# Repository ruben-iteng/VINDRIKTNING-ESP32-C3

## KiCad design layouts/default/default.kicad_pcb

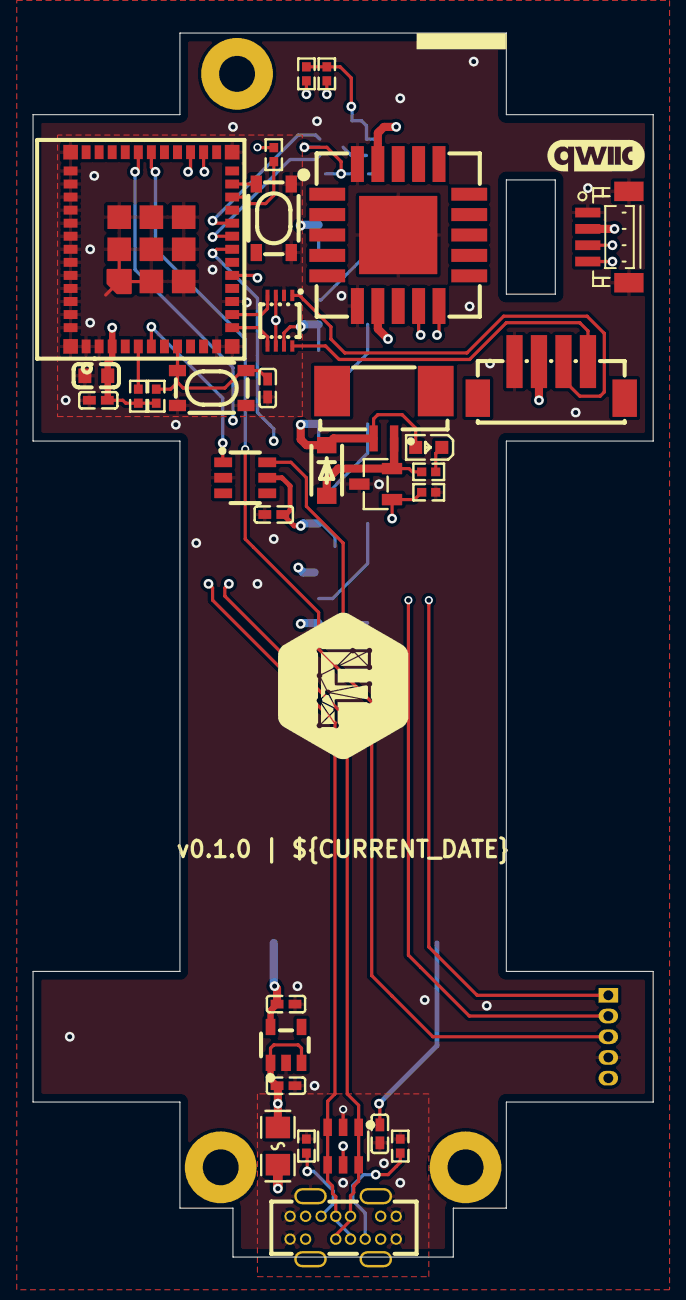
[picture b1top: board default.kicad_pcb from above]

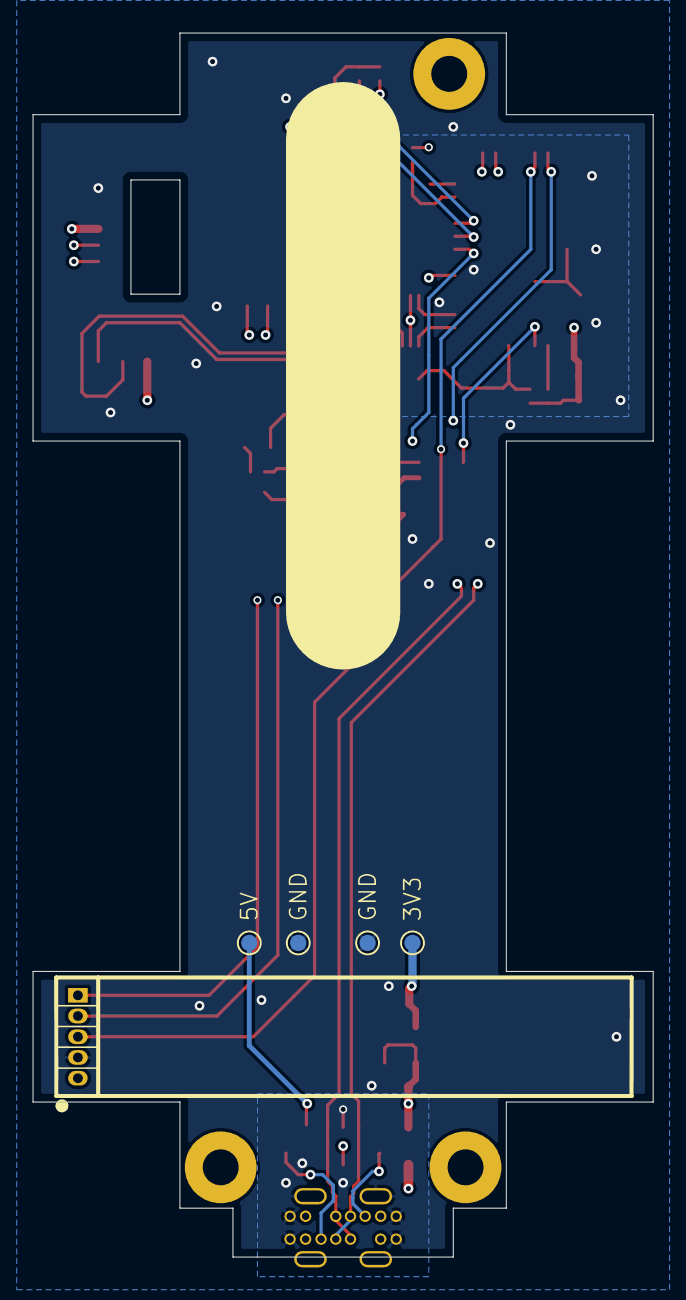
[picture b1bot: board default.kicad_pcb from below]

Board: 4 copper layers, 38.0 x 75.0 mm, 56 parts (18 on the bottom side), 31 nets.

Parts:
C1, C2, C3, C4, C5, C6, C7, C8, C9, C11, C13, C14: 100nF ±10% 16V X7R; C0402-b3ef17
C10: 22µF ±20% 6.3V X5R; C0603-bd72f6
C12: 1µF ±10% 25V X5R; C0402-b3ef17
CN1: CONN-SMD_BM04B-SRSS-TB-6963ef
D1: SOD-123F_L2.8-W1.8-LS3.7-RD-7788aa
FanConnector1: CONN-SMD_1.25-2P-ea2134
H1, H2, H3: MountingHole_2.2mm_M2_Pad
J2: CONN-SMD_ZH1.5-4AB-9aedad
LED1, LED2, LED3, LED4, LED5: LED-SMD_4P-L3.5-W2.8-BR-1-15b4e8
LOGO1: faebrykLogo_8x9mm
Q1: SOT-23-3_L2.9-W1.3-P1.90-LS2.4-BR-688f29
R1, R10: 1kΩ ±1% 62.5mW; R0402-56259e
R2, R6: 5.1kΩ ±1% 62.5mW; R0402-56259e
R3, R4, R5, R9, R11, R12: 10kΩ ±1% 62.5mW; R0402-56259e
TP1, TP2, TP3, TP4: TestPoint_Pad_D1.0mm
U1: LGA-20_L10.1-W10.1-P1.25-TL-a13bdd
U2: LDO 3.3V ±0% 850.5mA 320mV Vin max Iq 10µA; SOT-23-5_L2.9-W1.6-P0.95-LS2.8-BR-2dcca4
U3: SOT-23-6_L2.9-W1.6-P0.95-LS2.8-BR-bfc73b
U4: WSOF-6_L2.6-W1.6-P0.50-TL-EP-b2dfd8
U5, U7: KEY-SMD_4P-L4.2-W3.2-P2.20-LS4.6
U6: WIFIM-SMD_ESP32-C3-MINI-MINI-1U-1cb675
U8: SENSORM-TH_HLK-LD2410B-P-2a325e
U9: qwiic_6mm
U10: VSON8_L2.0-W2.3-P0.50-LS3.1-BL-9e6526
U11: 2V; LED0603-RD
U12: SOT-23-6_L2.9-W1.6-P0.95-LS2.8-BL-d2c740
U13: F0805-d5954a
X1: USB-C-TH_TYPE-C-USB-14P-1a34cb

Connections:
DVI: C13.1, R1.2, U4.5
cathode: R10.1, U11.1
gnd: C1.2, C2.2, C3.2, C4.2, C5.2, C6.2, C7.2, C8.2, C9.2, C10.2, C11.2, C12.2, C13.2, C14.2, CN1.0, CN1.1, J2.4, LED1.1, LED2.1, LED3.1, LED4.1, LED5.1, Q1.3, R2.2, R6.2, R9.2, TP2.1, TP4.1, U1.6, U1.20, U1.21, U2.2, U3.2, U4.2, U4.3, U4.7, U5.1, U5.2, U6.1, U6.2, U6.11, U6.14, U6.36, U6.37, U6.38, U6.39, U6.40, U6.41, U6.42, U6.43, U6.44, U6.45, U6.46, U6.47, U6.48, U6.49, U6.50, U6.51, U6.52, U6.53, U6.54, U6.55, U6.56, U6.57, U6.58, U6.59, U6.60, U6.61, U7.1, U7.2, U8.4, U10.2, U12.2, X1.0, X1.1, X1.7, X1.8, X1.14
hv: C1.1, C3.1, C4.1, C5.1, C6.1, C7.1, C8.1, C14.1, D1.1, FanConnector1.2, J2.3, LED1.3, LED2.3, LED3.3, LED4.3, LED5.3, TP3.1, U2.1, U2.3, U3.5, U8.5, U10.7, U11.2, U12.5, U13.2
hv-1: C2.1, C9.1, C10.1, C11.1, CN1.2, R1.1, R3.2, R4.2, R5.1, R11.2, R12.2, TP1.1, U1.7, U1.19, U2.5, U4.1, U6.3, U10.3, U10.6
hv-2: U13.1, X1.2, X1.6, X1.9, X1.13
line: LED1.4, LED2.2
line-1: CN1.4, R11.1, U1.9, U4.6, U6.20
line-2: LED4.4, LED5.2
line-3: Q1.1, R9.1, U6.18
line-4: R4.1, U6.22
line-6: U6.12, U10.5
line-7: U6.31, U8.2
line-8: CN1.3, R12.1, U1.10, U4.4, U6.19
line-9: U6.13, U10.4
line-10: LED2.4, LED3.2
line-11: R3.1, U6.5
line-12: U6.27, U12.3, U12.4, X1.4, X1.11
line-13: U6.16, U8.1
line-14: U3.1, U6.6
line-15: U6.26, U12.1, U12.6, X1.3, X1.10
line-16: R2.1, X1.12
line-17: LED1.2, U3.6
line-19: LED3.4, LED4.2
line-20: U6.30, U8.3
line-21: R6.1, X1.5
output: C12.1, R5.2, U6.8, U7.3, U7.4
output-1: U5.3, U5.4, U6.23
pin[0]: J2.1, U10.8
pin[1]: J2.2, U10.1
vindriktning_interface.fan_controller-gnd: D1.2, FanConnector1.1, Q1.2, R10.2

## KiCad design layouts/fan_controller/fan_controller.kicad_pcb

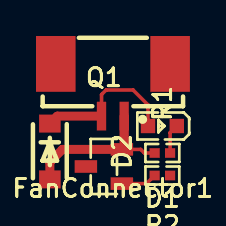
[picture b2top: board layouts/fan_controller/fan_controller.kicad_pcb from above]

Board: 2 copper layers, 6 parts (0 on the bottom side), 4 nets.

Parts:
D1: 2V; LED0603-RD
D2: SOD-123F_L2.8-W1.8-LS3.7-RD-7788aa
FanConnector1: CONN-SMD_1.25-2P-ea2134
Q1: SOT-23-3_L2.9-W1.3-P1.90-LS2.4-BR-688f29
R1: 10kΩ ±1% 62.5mW; R0402-56259e
R2: 1kΩ ±1% 62.5mW; R0402-56259e

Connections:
anode: D1.2, D2.1, FanConnector1.2
cathode: D1.1, R2.1
gate: Q1.1, R1.1
gnd: D2.2, FanConnector1.1, Q1.2, R2.2

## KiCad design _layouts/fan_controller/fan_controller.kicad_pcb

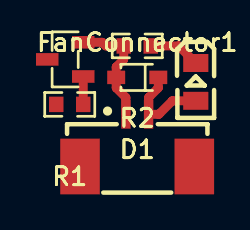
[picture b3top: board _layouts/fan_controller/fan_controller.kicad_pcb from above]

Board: 2 copper layers, 6 parts (0 on the bottom side), 4 nets.

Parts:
D1: 450mV; SOD-323_L1.8-W1.3-LS2.5-RD-b55baa
D2: LED0805-R-RD-d1137b
FanConnector1: CONN-SMD_1.25-2P-ea2134
Q1: SOT-23-3_L2.9-W1.3-P1.90-LS2.4-BL-1-fcaf94
R1, R2: 10kΩ ±1% 100mW; R0603-ebcab9

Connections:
cathode: D2.2, R2.1
gnd: D1.2, FanConnector1.1, Q1.2, R2.2
hv: D1.1, D2.1, FanConnector1.2
line: Q1.1, R1.1

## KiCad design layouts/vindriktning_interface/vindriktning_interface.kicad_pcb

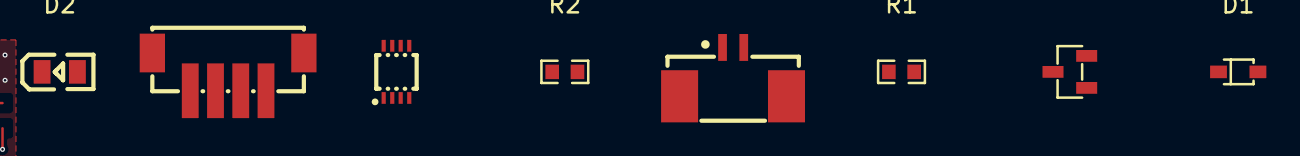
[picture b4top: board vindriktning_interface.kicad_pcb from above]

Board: 2 copper layers, 8 parts (0 on the bottom side), 9 nets.

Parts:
D1: 450mV; SOD-323_L1.8-W1.3-LS2.5-RD-b55baa
D2: LED0805-R-RD-d1137b
FanConnector1: CONN-SMD_1.25-2P-ea2134
J1: CONN-SMD_ZH1.5-4AB-9aedad
Q1: SOT-23-3_L2.9-W1.3-P1.90-LS2.4-BR-688f29
R1, R2: 10kΩ ±1% 100mW; R0603-ebcab9
U1: VSON8_L2.0-W2.3-P0.50-LS3.1-BL-9e6526

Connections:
cathode: D2.2, R2.1
fan_controller-gnd: D1.2, FanConnector1.1, Q1.2, R2.2
fan_controller-hv: D1.1, D2.1, FanConnector1.2
gnd-1: J1.4, U1.2
hv: J1.3, U1.7
hv-1: U1.3, U1.6
line: J1.2, U1.1
line-1: J1.1, U1.8
line-2: Q1.1, R1.1

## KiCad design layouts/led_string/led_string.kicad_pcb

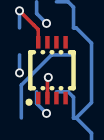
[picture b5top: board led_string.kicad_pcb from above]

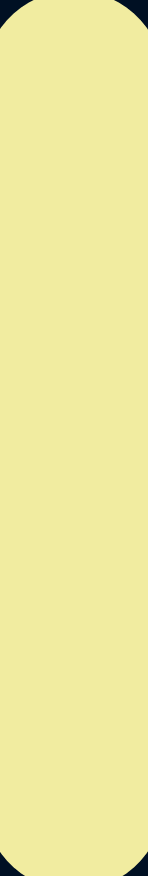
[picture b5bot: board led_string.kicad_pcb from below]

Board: 2 copper layers, 19 parts (18 on the bottom side), 12 nets.

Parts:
C1, C2, C3, C4, C5, C6, C7, C8, C9: 100nF ±10% 16V X7R; C0402-b3ef17
LED1, LED2, LED3, LED4, LED5, LED6, LED7, LED8, LED9: LED-SMD_4P-L3.5-W2.8-BR-1-15b4e8
U1: VSON8_L2.0-W2.3-P0.50-LS3.1-BL-9e6526

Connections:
gnd: C1.2, C2.2, C3.2, C4.2, C5.2, C6.2, C7.2, C8.2, C9.2, LED1.1, LED2.1, LED3.1, LED4.1, LED5.1, LED6.1, LED7.1, LED8.1, LED9.1, U1.2
hv: U1.3, U1.6
hv-1: C1.1, C2.1, C3.1, C4.1, C5.1, C6.1, C7.1, C8.1, C9.1, LED1.3, LED2.3, LED3.3, LED4.3, LED5.3, LED6.3, LED7.3, LED8.3, LED9.3, U1.7
line: LED4.4, LED5.2
line-1: LED5.4, LED6.2
line-2: LED1.2, U1.8
line-3: LED7.4, LED8.2
line-4: LED6.4, LED7.2
line-5: LED1.4, LED2.2
line-7: LED2.4, LED3.2
line-8: LED8.4, LED9.2
line-9: LED3.4, LED4.2

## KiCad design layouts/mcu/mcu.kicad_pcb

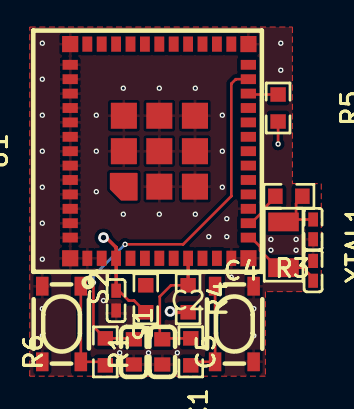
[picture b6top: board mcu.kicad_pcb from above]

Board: 2 copper layers, 15 parts (0 on the bottom side), 11 nets.

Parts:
C1, C5: 100nF ±10% 50V X7R; C0603-bd72f6
C2: 1µF ±10% 25V X5R; C0402-b3ef17
C3, C4: 20pF ±5% 50V C0G; C0402-b3ef17
R1, R2, R4, R5, R6: 10kΩ ±1% 100mW; R0603-ebcab9
R3: 0Ω 100mW; R0603-ebcab9
S1, S2: KEY-SMD_4P-L4.2-W3.2-P2.20-LS4.6-a2ccf0
U1: WIFIM-SMD_ESP32-C3-MINI-MINI-1U-1cb675
XTAL1: CRYSTAL-SMD_L3.2-W1.5-1-214bf9

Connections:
gnd: C1.2, C2.2, C3.2, C4.2, C5.2, S1.3, S1.4, S2.3, S2.4, U1.1, U1.2, U1.11, U1.14, U1.36, U1.37, U1.38, U1.39, U1.40, U1.41, U1.42, U1.43, U1.44, U1.45, U1.46, U1.47, U1.48, U1.49, U1.50, U1.51, U1.52, U1.53, U1.54, U1.55, U1.56, U1.57, U1.58, U1.59, U1.60, U1.61
hv: C2.1, R2.2, R4.2, R5.2, U1.3
mcu-line: C1.1, R1.2, R2.1, U1.8
mcu-line-1: C4.1, U1.12, XTAL1.2
mcu-line-4: R3.2, U1.13
mcu-line-5: R4.1, U1.5
mcu-line-7: C5.1, R6.2, U1.23
mcu-line-9: R5.1, U1.22
mcu.boot_switch-line: R1.1, S1.1, S1.2
mcu.low_speed_crystal_clock-net: C3.1, R3.1, XTAL1.1
mcu.reset_switch-line: R6.1, S2.1, S2.2

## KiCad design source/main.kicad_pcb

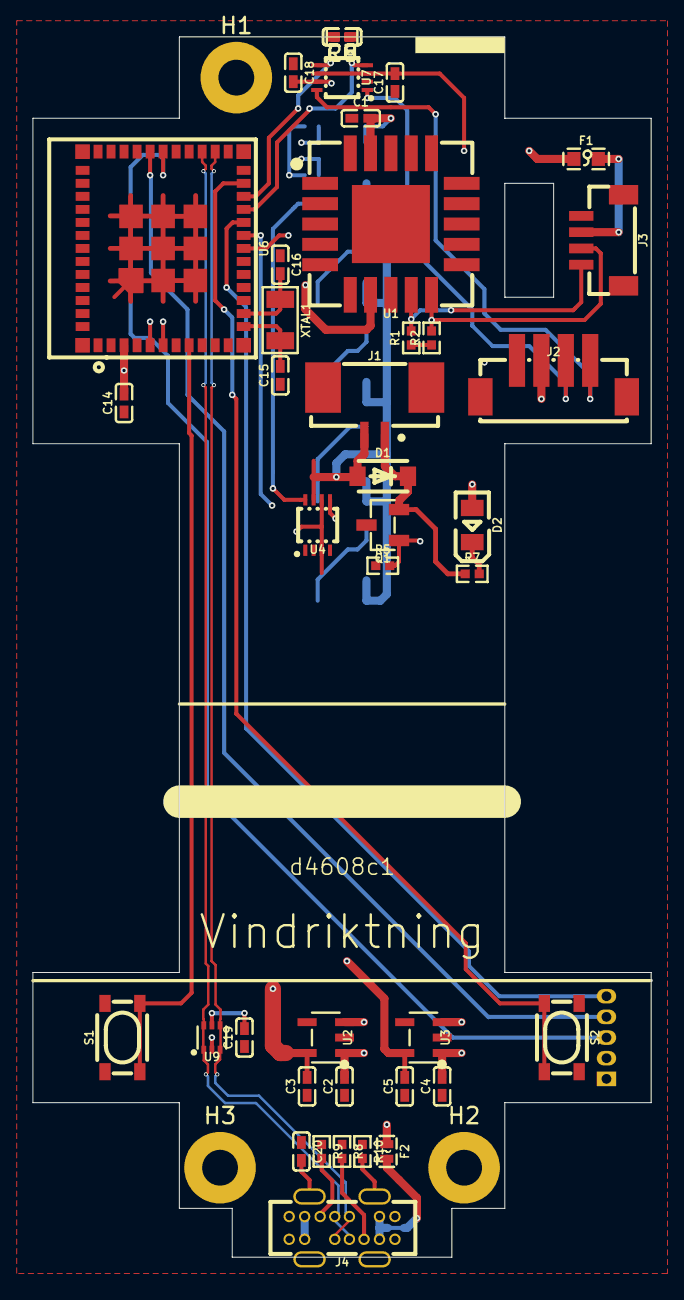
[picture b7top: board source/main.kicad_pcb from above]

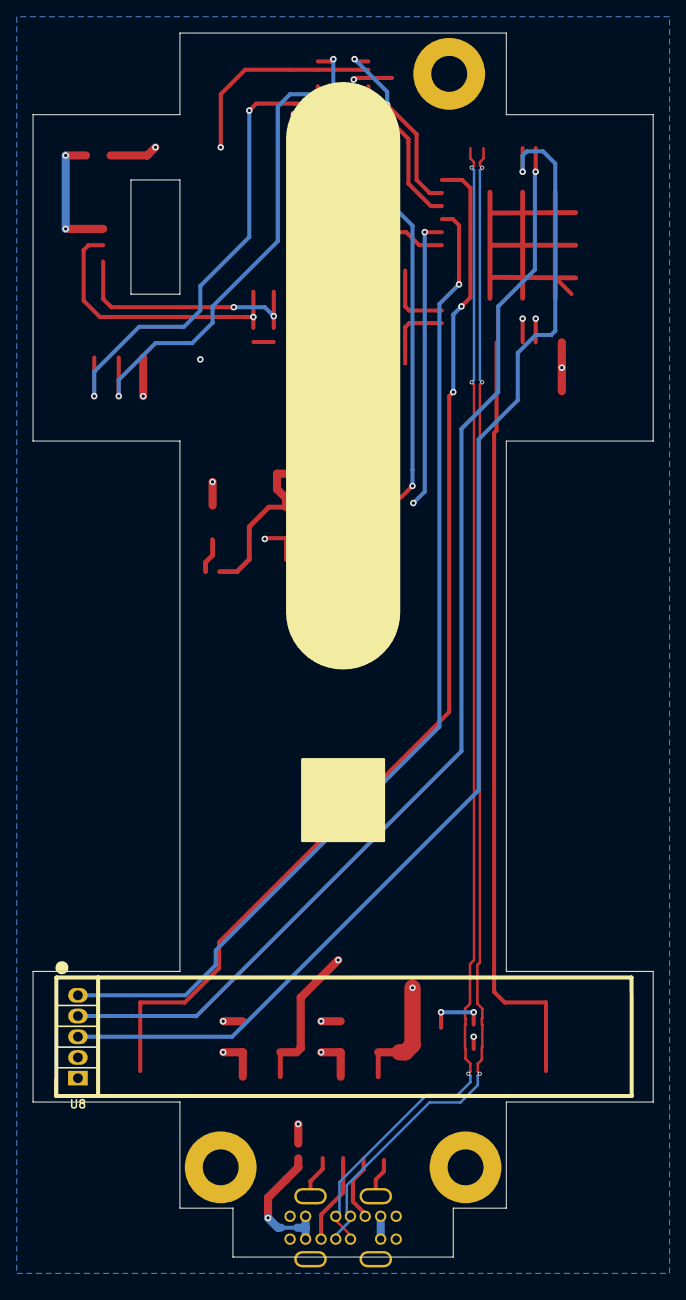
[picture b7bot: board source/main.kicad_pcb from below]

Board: 4 copper layers, 38.0 x 75.0 mm, 59 parts (15 on the bottom side), 31 nets.

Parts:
C1, C2, C3, C4, C5, C6, C7, C8, C9, C13, C14, C17, C18, C19, C20, C21, C22, C23: 100nF 16V X7R; C0402
C15, C16: 15pF 50V C0G; C0402
D1: 1.1V; SOD-123F_L2.8-W1.8-LS3.7-RD
D2: 2V; LED0805-R-RD
F1: Fuse; F0603
F2: Fuse; F0402
H1, H2, H3: Mounting_Hole; MountingHole_2.2mm_M2_Pad
J1: pf_533984002; CONN-SMD_1.25-2P
J2: B4B_ZR_SM4_TF; CONN-SMD_ZH1.5-4AB
J3: QWIIC; CONN-SMD_BM04B-SRSS-TBT-LF-SN
J4: USB_Type_C_Receptacle_14_pin_Vertical; USB-C-TH_TYPE-C-USB-14P
LED1, LED2, LED3, LED4, LED5: XL_3528RGBW_WS2812B; LED-SMD_4P-L3.5-W2.8-BR-1
Q1: MOSFET; SOT-23-3_L2.9-W1.3-P1.90-LS2.4-BR
R1, R2, R3, R4, R5, R6: 100Ω; R0402
R7: 2.2kΩ; R0402
R8, R9: 5.1kΩ; R0402
R10: 1MΩ; R0402
S1, S2: Button; KEY-SMD_4P-L4.2-W3.2-P2.20-LS4.6
U1: SCD40; LGA-20_L10.1-W10.1-P1.25-TL
U2: LDO 3.3V ±2% Vin max 4.8V - 5.2V Iq; SOT-23-5_L3.0-W1.7-P0.95-LS2.8-BL
U3: LDO 3.3V Vin max 4.8V - 5.2V Iq; SOT-23-5_L3.0-W1.7-P0.95-LS2.8-BL
U4, U7: TXS0102DCUR; VSON8_L2.0-W2.3-P0.50-LS3.1-BL
U5: BH1750FVI_TR; WSOF-6_L2.6-W1.6-P0.50-TL-EP
U6: ESP32_C3_MINI_1; WIFIM-SMD_ESP32-C3-MINI-MINI-1U
U8: HLK_LD2410B_P; SENSORM-TH_HLK-LD2410B-P
U9: USB2_0_ESD_Protection; SOT-666-6_L1.6-W1.2-P0.50-LS1.6-BL
XTAL1: Crystal; CRYSTAL-SMD_L3.2-W1.5-1

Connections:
3V3_MCU: C3.1, C14.1, R6.2, U2.5, U6.3
3V3_PERIPHERAL: C1.1, C5.1, C8.1, C13.1, C17.1, F1.2, R3.2, R4.2, U1.7, U1.19, U3.5, U4.3, U4.6, U5.1, U7.3, U7.6
5V: C2.1, C4.1, C6.1, C7.1, C9.1, C18.1, C19.1, C21.1, C22.1, C23.1, D1.2, D2.1, F2.2, J1.2, J2.3, LED1.3, LED2.3, LED3.3, LED4.3, LED5.3, U2.1, U3.1, U4.7, U7.7, U8.5, U9.5
C20-1-J4-0-R10-1: C20.1, J4.0, R10.1
CHIP_EN: R6.1, S1.1, S1.2, U6.8
D2-2-R7-1: D2.2, R7.1
F1-1-J3-2: F1.1, J3.2
FAN_OUT-: D1.1, J1.1, Q1.2, R7.2
GND: C1.2, C2.2, C3.2, C4.2, C5.2, C6.2, C7.2, C8.2, C9.2, C13.2, C14.2, C15.2, C16.2, C17.2, C18.2, C19.2, C20.2, C21.2, C22.2, C23.2, J2.4, J3.1, J4.1, J4.7, J4.8, J4.14, LED1.1, LED2.1, LED3.1, LED4.1, LED5.1, Q1.3, R5.2, R8.2, R9.2, R10.2, S1.3, S1.4, S2.3, S2.4, U1.6, U1.20, U1.21, U2.2, U3.2, U4.2, U5.3, U6.1, U6.2, U6.11, U6.14, U6.36, U6.37, U6.38, U6.39, U6.40, U6.41, U6.42, U6.43, U6.44, U6.45, U6.46, U6.47, U6.48, U6.49, U6.50, U6.51, U6.52, U6.53, U6.54, U6.55, U6.56, U6.57, U6.58, U6.59, U6.60, U6.61, U7.2, U8.4, U9.2
LED1-2-U4-8: LED1.2, U4.8
LED1-4-LED2-2: LED1.4, LED2.2
LED2-4-LED3-2: LED2.4, LED3.2
LED3-4-LED4-2: LED3.4, LED4.2
LED4-4-LED5-2: LED4.4, LED5.2
MCU_GPIO0: C15.1, U6.12, XTAL1.1
MCU_GPIO1: C16.1, U6.13, XTAL1.2
MCU_GPIO4: Q1.1, R5.1, U6.18
MCU_GPIO5: U4.5, U6.19
MCU_GPIO6: U6.20, U8.1
MCU_GPIO9: S2.1, S2.2, U6.23
R1-2-R2-2: R1.2, R2.2
SCL: J3.4, R1.1, R3.1, U1.9, U5.6
SDA: J3.3, R2.1, R4.1, U1.10, U5.4
U2-3-U3-3: U2.3, U3.3
USB_CC1: J4.12, R8.1
USB_CC2: J4.5, R9.1
USB_DN: J4.3, J4.10, U9.3, U9.4
USB_DP: J4.4, J4.11, U9.1, U9.6
USF_PM_SENSOR_LEVEL_SHIFTER_RX: J2.1, U7.8
USF_PM_SENSOR_LEVEL_SHIFTER_TX: J2.2, U7.1
VBUS: F2.1, J4.2, J4.6, J4.9, J4.13

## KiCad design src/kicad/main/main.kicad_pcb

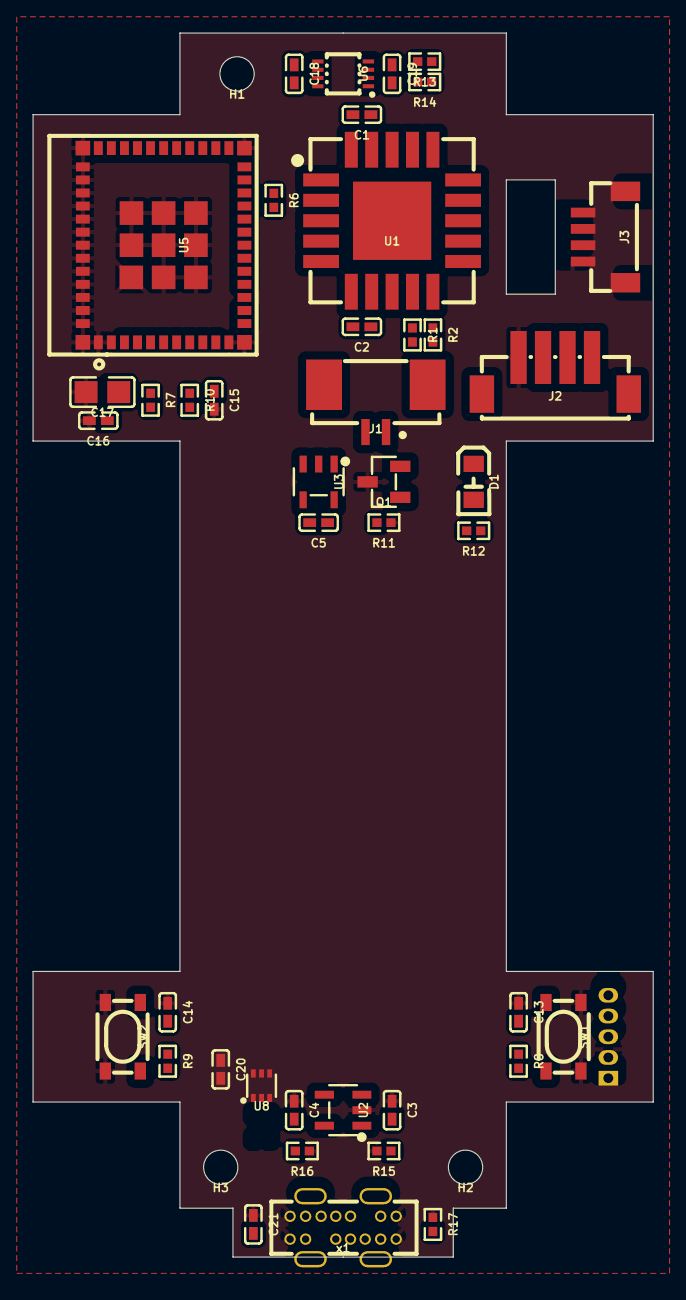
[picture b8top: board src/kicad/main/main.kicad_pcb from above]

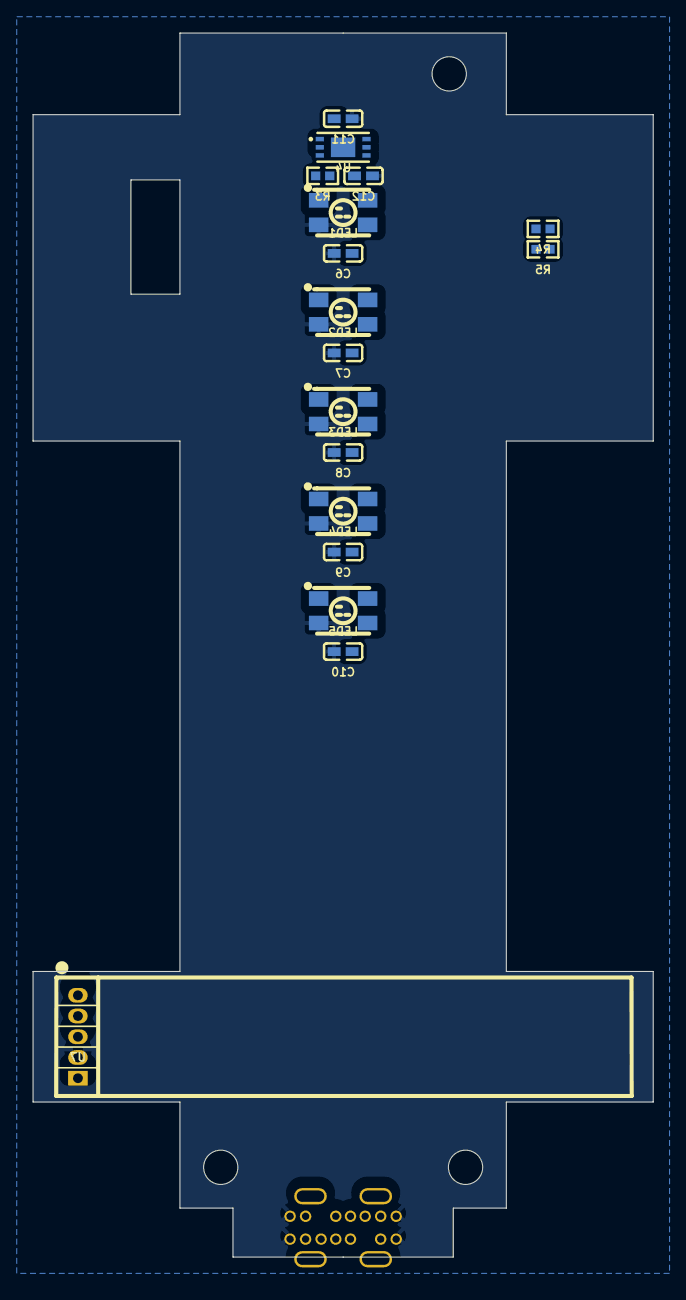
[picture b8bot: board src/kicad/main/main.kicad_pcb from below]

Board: 4 copper layers, 38.0 x 75.0 mm, 62 parts (17 on the bottom side), 33 nets, no tracks yet.

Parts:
C1, C5, C6, C7, C8, C9, C10, C11, C13, C14, C16, C18, C19, C21: 100nF; C0402
C2: 4.7µF; C0402
C3, C4, C12, C15, C20: 1µF; C0402
C17: 10µF; C0805
D1: LED; LED0805-RD_RED
H1, H2, H3: Mounting_Hole; MountingHole_2.1mm
J1: pf_533984002; CONN-SMD_1.25-2P
J2: B4B_ZR_SM4_TF; CONN-SMD_ZH1.5-4AB
J3: QWIIC; CONN-SMD_BM04B-SRSS-TBT-LF-SN
LED1, LED2, LED3, LED4, LED5: XL_3528RGBW_WS2812B; LED-SMD_4P-L3.5-W2.8-BR-1
Q1: MOSFET; SOT-23-3_L2.9-W1.3-P1.90-LS2.4-BR
R1, R2, R4, R5, R6, R7, R8, R9, R10: 10kΩ; R0402
R3, R12: 1kΩ; R0402
R11: 100kΩ; R0402
R13, R14: 390Ω; R0402
R15, R16: 5.1kΩ; R0402
R17: 1MΩ; R0402
SW1, SW2: _Switch; KEY-SMD_4P-L4.2-W3.2-P2.20-LS4.6
U1: SCD40; LGA-20_L10.1-W10.1-P1.25-TL
U2: ME6211C33M5G_N; SOT-23-5_L3.0-W1.7-P0.95-LS2.8-BL
U3: pf_74AHCT2G125; SC-74A-5_L2.9-W1.6-P0.95-LS2.8-BR
U4: BH1750FVI_TR; WSOF-6_L2.6-W1.6-P0.50-TL-EP
U5: ESP32_C3_MINI_1_VIND; WIFIM-SMD_ESP32-C3-MINI-MINI-1U
U6: TXS0102DCUR; VSON8_L2.0-W2.3-P0.50-LS3.1-BL
U7: HLK_LD2410B_P; SENSORM-TH_HLK-LD2410B-P
U8: USBLC6_2P6; SOT-666-6_L1.6-W1.2-P0.50-LS1.6-BL
x1: USB_Type_C_Receptacle_14_pin_Vertical; USB-C-TH_TYPE-C-USB-14P

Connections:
3V3: C4.1, C11.1, C16.1, C17.1, J3.2, R1.2, R2.2, R3.2, R4.2, R5.2, R6.2, R7.2, R10.2, U2.5, U4.1, U5.3
C1-1-C2-1-U1-19-U1-7: C1.1, C2.1, U1.7, U1.19
C1-2-C2-2-U1-20-U1-21-U1-6: C1.2, C2.2, U1.6, U1.20, U1.21
C5-1-U3-5: C5.1, U3.5
C5-2-U3-1-U3-3: C5.2, U3.1, U3.3
C12-1-R3-1-U4-5: C12.1, R3.1, U4.5
C13-1-R8-2-SW1-1-SW1-2: C13.1, R8.2, SW1.1, SW1.2
C14-1-R9-2-SW2-1-SW2-2: C14.1, R9.2, SW2.1, SW2.2
C15-1-R10-1-R8-1-R9-1-U5-8: C15.1, R8.1, R9.1, R10.1, U5.8
C18-1-C19-1-U6-3-U6-7: C18.1, C19.1, U6.3, U6.7
C18-2-C19-2-U6-2-U6-6: C18.2, C19.2, U6.2, U6.6
C21-1-R17-1-x1-0: C21.1, R17.1, x1.0
D1-2-R12-2: D1.2, R12.2
GND: C3.2, C4.2, C6.2, C7.2, C8.2, C9.2, C10.2, C11.2, C12.2, C13.2, C14.2, C15.2, C16.2, C17.2, C20.2, C21.2, J2.4, J3.1, LED1.2, LED2.2, LED3.2, LED4.2, LED5.2, Q1.3, R11.2, R15.2, R16.2, R17.2, SW1.3, SW1.4, SW2.3, SW2.4, U2.2, U4.3, U5.1, U5.2, U5.11, U5.14, U5.36, U5.37, U5.38, U5.39, U5.40, U5.41, U5.42, U5.43, U5.44, U5.45, U5.46, U5.47, U5.48, U5.49, U5.50, U5.51, U5.52, U5.53, U7.4, U8.2, x1.1, x1.7, x1.8, x1.14
J1-1-Q1-2: J1.1, Q1.2
J3-3-R1-1-R4-1-U1-10-U4-4-U5-19: J3.3, R1.1, R4.1, U1.10, U4.4, U5.19
J3-4-R2-1-R5-1-U1-9-U4-6-U5-18: J3.4, R2.1, R5.1, U1.9, U4.6, U5.18
LED1-1-U3-4: LED1.1, U3.4
LED1-4-LED2-1: LED1.4, LED2.1
LED2-4-LED3-1: LED2.4, LED3.1
LED3-4-LED4-1: LED3.4, LED4.1
LED4-4-LED5-1: LED4.4, LED5.1
Q1-1-R11-1-U5-21: Q1.1, R11.1, U5.21
R6-1-U5-22: R6.1, U5.22
R7-1-U5-5: R7.1, U5.5
R15-1-x1-12: R15.1, x1.12
R16-1-x1-5: R16.1, x1.5
U5-12-U7-3: U5.12, U7.3
U5-13-U7-2: U5.13, U7.2
U5-20-U7-1: U5.20, U7.1
U5-26-U8-3-U8-4-x1-10-x1-3: U5.26, U8.3, U8.4, x1.3, x1.10
U5-27-U8-1-U8-6-x1-11-x1-4: U5.27, U8.1, U8.6, x1.4, x1.11
VBUS: C3.1, C6.1, C7.1, C8.1, C9.1, C10.1, C20.1, J1.2, J2.3, LED1.3, LED2.3, LED3.3, LED4.3, LED5.3, U2.1, U2.3, U7.5, U8.5, x1.2, x1.6, x1.9, x1.13

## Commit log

2023-10-09 Add components
2023-11-27 Update a lot of stuff
2023-11-27 Fix esphome config i2c
2023-12-04 Fix: logic references, missing FAN component, import sort
    Add: ESPHome gpio config, ESPHome digitalLED config, ESPHome PM106 config, uart voltage dropper (WIP), manually rename GND net
2023-12-04 Fix: python recursion depth
2023-12-18 Use latest faebryk features
2024-01-29 Add JLCPCB DRC
2024-01-29 Bugfixes and additions:
    fix:
    - component placement
    - var naming
    - increase recursion limit
    - connections
    - linting errors
2024-01-29 Partial routing
    Fix coordinate typo
2024-06-14 update .gitignore and pre-commit
2024-06-14 WIP: update project for faebryk 3.0.1
2024-07-05 Update for latest faebryk
2024-07-06 Port layout (wip)
2024-08-13 Various fixes and changes
2024-08-28 Deps: update with new faebryk
2024-08-28 WIP: upgrade to latest faebryk
2024-08-29 dos2unix
2024-08-29 midway faebryk update
2024-08-29 Fix some imports and units
2024-08-29 made pixels int
2024-08-29 fix deps & fix imports
2024-08-29 make build (till picker)
2024-08-29 capacitor stuff
2024-08-29 Add: missing crystal picker
2024-08-29 Fix: digital led connections
2024-08-29 Add: missing connection to fan
2024-08-30 debug
2024-08-30 fix power source short
2024-08-30 Fix some layout
    - Add named net for fan
    - Add part db to gitignore
2024-09-02 Finish trace routing
2024-09-02 genral fixes and improvements
2024-09-11 Move logo
2024-09-11 fix minor issues
2024-09-11 Fix holes
2024-09-11 Rerun
2025-02-14 Migrate fan controller to new ato/faebll
2025-02-14 Migrate DigitalLED, rename to LEDString
2025-02-14 Migrate PCBMount
2025-02-14 Add PM1006 interface
2025-02-14 Migrate app/base
2025-02-15 Add MCU as build target
    use this ato branch to fix build:
    https://github.com/atopile/atopile/pull/979
2025-02-16 fix typo
2025-02-17 Migrate layout partially
    omit routing and zones amongst others
2025-02-17 Regenerate layouts
2025-02-23 Hide all designators
2025-02-23 Let default layout determine designator visibility
2025-02-23 Update layouts
2025-02-23 Add layout for LEDString
2025-02-23 Add and remove pinmaps
    Add missing supplier partnos
2025-02-23 update minimum ato version
2025-02-23 Update layout
2025-02-24 Recover the original README
2025-02-28 Led string: fix vertical offset
2025-02-28 Layouts: mcu: place and route mcu, add jlc design rules
2025-02-28 Layouts: led string: fix led string layout, increase leds to 9
2025-02-28 Layouts: place light sensor between LEDs, add rule areas
2025-02-28 do some layouts
2025-03-01 Try to fix fuses
2025-03-13 App: connect fuse correctly (breaks build)
2025-03-13 MCU: fix picker error for alias-is'ed 0R resistor
2025-05-30 Make it build with ato 0.8.x
    - refactor modules
    - clean up modules and structure
    - convert some from fabll to ato
2025-06-03 Finish layout, swap to ufl version of esp32c3
2025-08-17 Update README.md
    Remove email from readme
